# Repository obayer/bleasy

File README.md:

BLEasy
======

Arduino/HM10 based sensor plattform

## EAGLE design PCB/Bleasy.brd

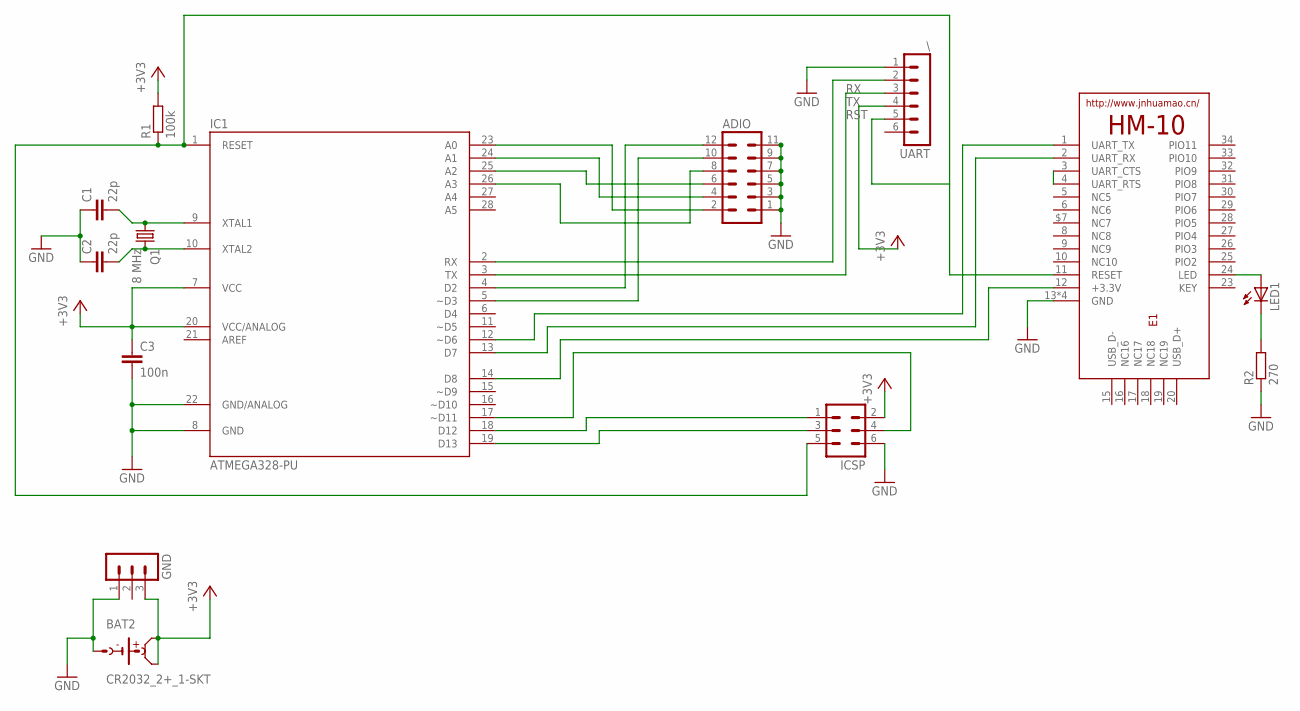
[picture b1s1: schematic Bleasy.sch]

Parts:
ADIO: MA06-2
BAT2: CR2032_2+_1-SKT; CR2032-SOCKET-THT
C1, C2: 22p; C025-025X050
C3: 100n; C025-025X050
E1: HM-10-BOARD; 26.9X13X2.2_BOARD
GND: MA03-1
IC1: ATMEGA328-PU; DIL28-3
ICSP: MA03-2
LED1: LED3MM
Q1: 8 MHz; HC49U70
R1: 100k; R1206
R2: 270; R1206
UART: \; MA06-1

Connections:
+3V3: BAT2.2 (POS2), BAT2.3 (POS1), C3.1, GND.3, IC1.7 (VCC), IC1.20 (VCC/ANALOG), ICSP.2, R1.2, UART.4
GND: ADIO.1, ADIO.3, ADIO.5, ADIO.7, ADIO.9, ADIO.11, BAT2.1 (NEG), C1.1, C2.1, C3.2, E1.13 (GND), E1.14 (GND), E1.21 (GND), E1.22 (GND), GND.1, IC1.8 (GND), IC1.22 (GND/ANALOG), ICSP.6, R2.1, UART.1
HM10_RX: E1.2 (UART_RX), IC1.13 (D7)
HM10_TX: E1.1 (UART_TX), IC1.12 (~D6)
MISO: IC1.18 (D12), ICSP.1
unnamed: C2.2, IC1.10 (XTAL2), Q1.2
unnamed: C1.2, IC1.9 (XTAL1), Q1.1
unnamed: IC1.17 (~D11), ICSP.4
unnamed: ADIO.12, IC1.4 (D2)
unnamed: ADIO.10, IC1.5 (~D3)
unnamed: E1.24 (LED), LED1.A
unnamed: LED1.K (C), R2.2
unnamed: E1.12 (+3.3V), IC1.14 (D8)
unnamed: ADIO.2, IC1.23 (A0)
unnamed: ADIO.4, IC1.24 (A1)
unnamed: ADIO.6, IC1.25 (A2)
unnamed: ADIO.8, IC1.26 (A3)
unnamed: E1.3 (UART_CTS), E1.4 (UART_RTS)
RST: E1.11 (RESET), IC1.1 (RESET), ICSP.5, R1.1, UART.5
RX: IC1.2 (RX), UART.2
SCK: IC1.19 (D13), ICSP.3
TX: IC1.3 (TX), UART.3

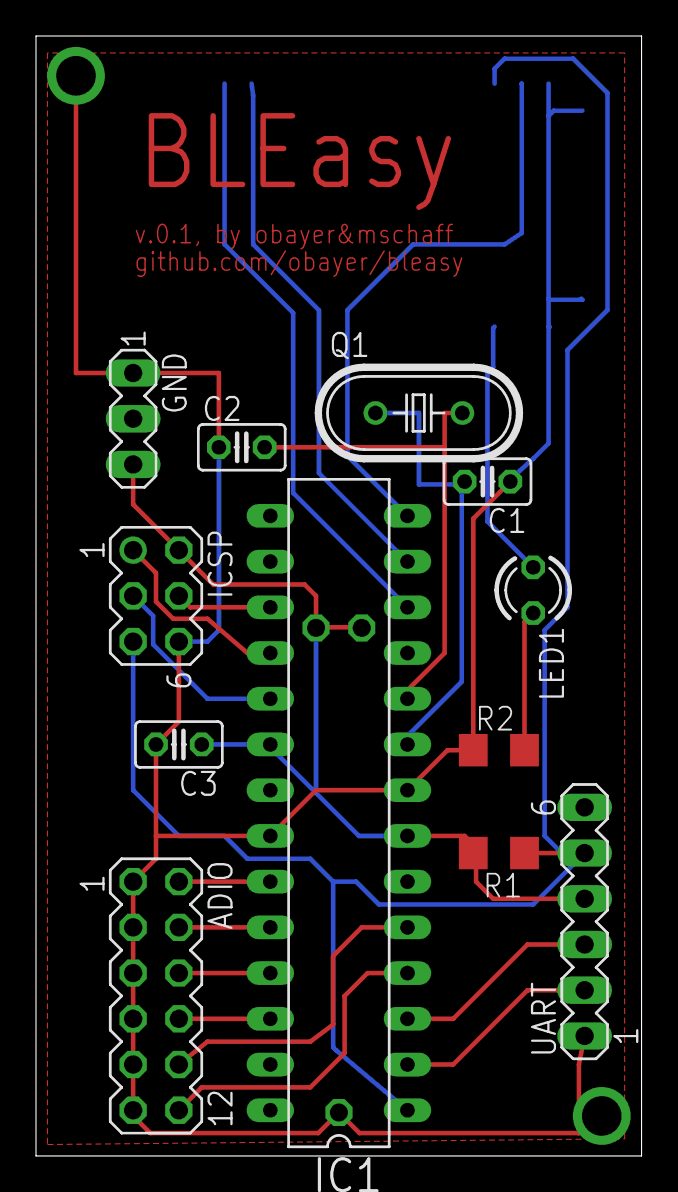
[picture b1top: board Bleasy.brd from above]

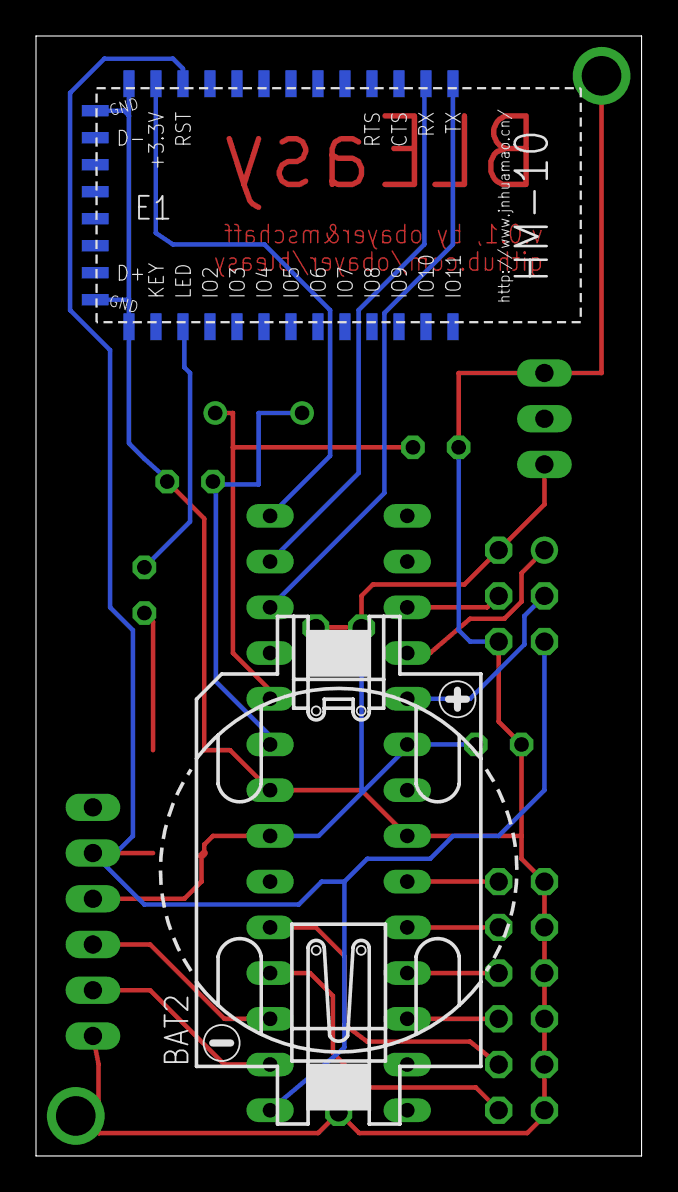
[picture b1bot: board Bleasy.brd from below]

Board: 2 copper layers, 33.6 x 62.2 mm, 14 parts (2 on the bottom side), 22 nets.

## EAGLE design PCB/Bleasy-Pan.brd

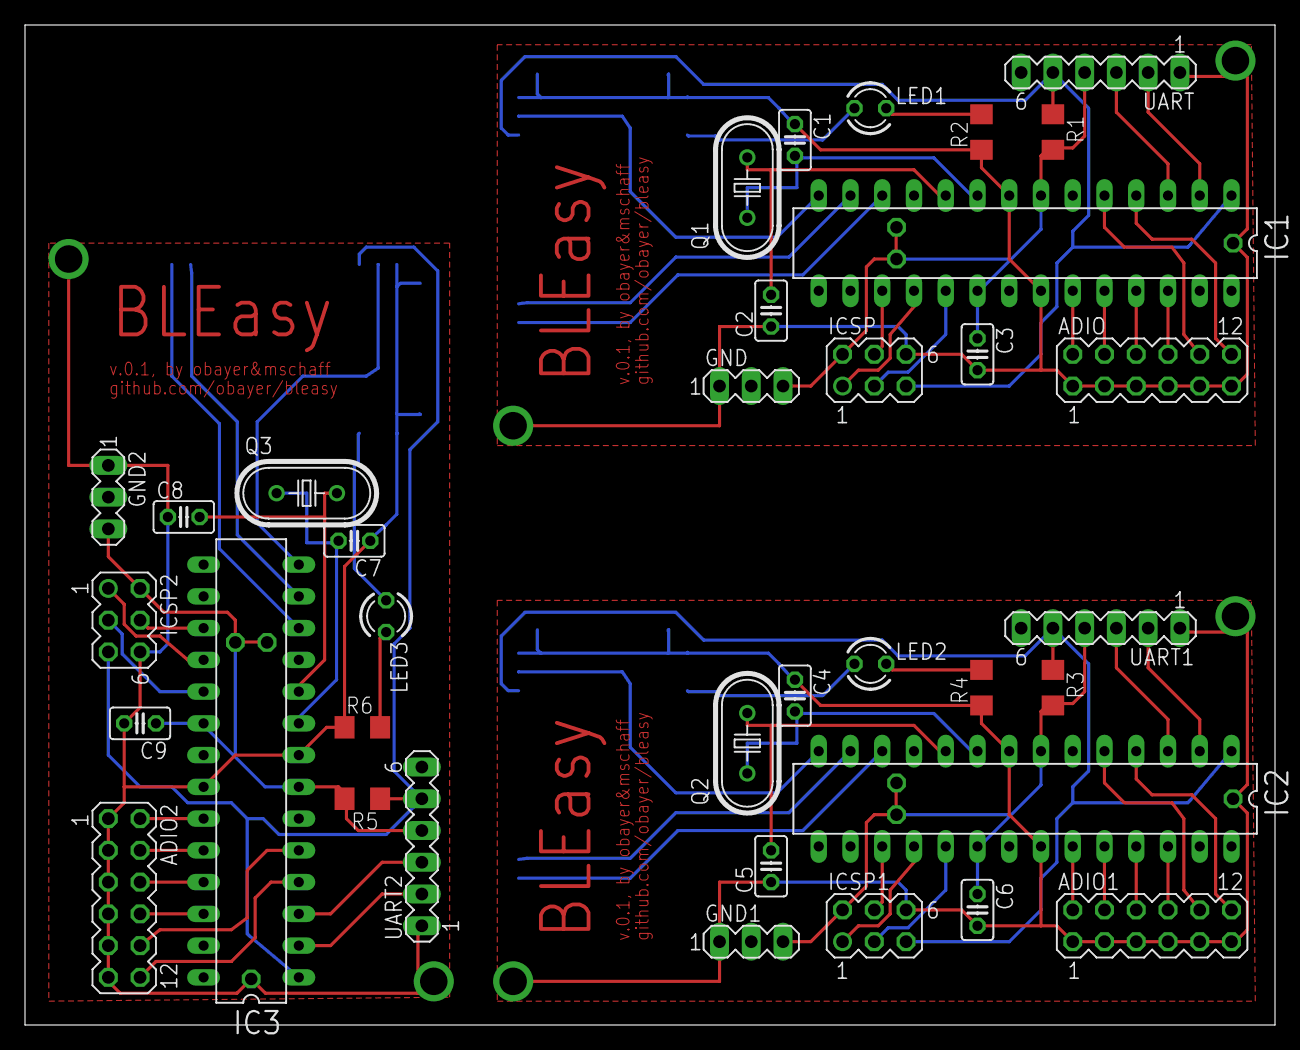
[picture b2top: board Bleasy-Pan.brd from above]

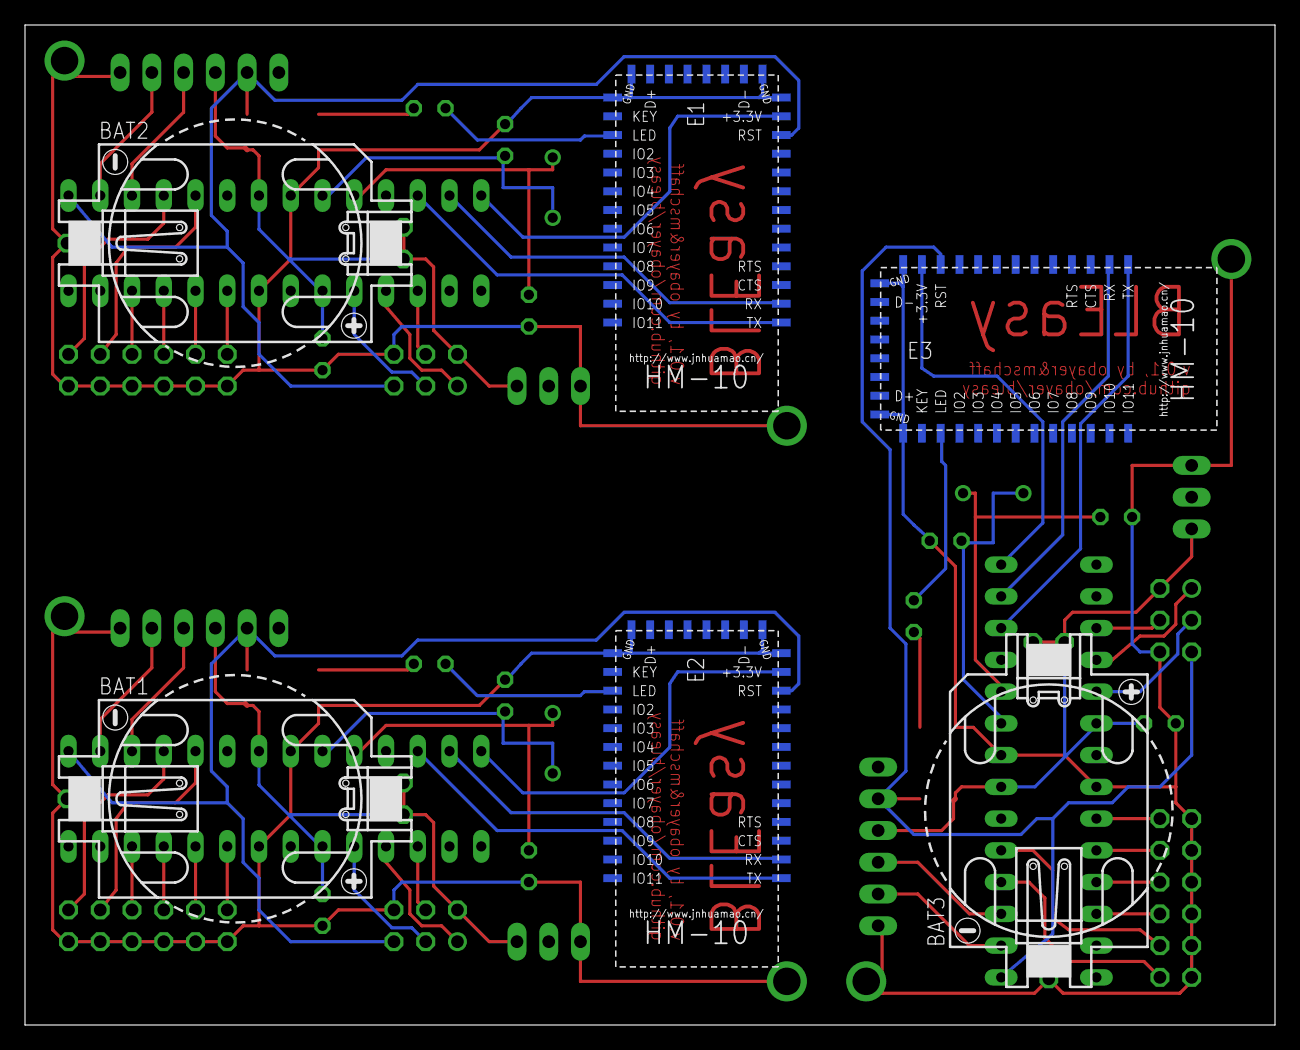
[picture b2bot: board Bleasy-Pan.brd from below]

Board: 2 copper layers, 100.0 x 80.0 mm, 42 parts (6 on the bottom side), 66 nets.

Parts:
ADIO, ADIO1, ADIO2: MA06-2
BAT1, BAT2, BAT3: CR2032_2+_1-SKT; CR2032-SOCKET-THT
C1, C2, C4, C5, C7, C8: 22p; C025-025X050
C3, C6, C9: 100n; C025-025X050
E1, E2, E3: HM-10-BOARD; 26.9X13X2.2_BOARD
GND, GND1, GND2: MA03-1
IC1, IC2, IC3: ATMEGA328-PU; DIL28-3
ICSP, ICSP1, ICSP2: MA03-2
LED1, LED2, LED3: LED3MM
Q1, Q2, Q3: 8 MHz; HC49U70
R1, R3, R5: 100k; R1206
R2, R4, R6: 270; R1206
UART, UART1, UART2: \; MA06-1

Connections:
+3V1: BAT1.2, BAT1.3, C6.1, GND1.3, IC2.7, IC2.20, ICSP1.2, R3.2, UART1.4
+3V2: BAT3.2, BAT3.3, C9.1, GND2.3, IC3.7, IC3.20, ICSP2.2, R5.2, UART2.4
+3V3: BAT2.2, BAT2.3, C3.1, GND.3, IC1.7, IC1.20, ICSP.2, R1.2, UART.4
GND: ADIO.1, ADIO.3, ADIO.5, ADIO.7, ADIO.9, ADIO.11, BAT2.1, C1.1, C2.1, C3.2, E1.13, E1.14, E1.21, E1.22, GND.1, IC1.8, IC1.22, ICSP.6, R2.1, UART.1
GND1: ADIO1.1, ADIO1.3, ADIO1.5, ADIO1.7, ADIO1.9, ADIO1.11, BAT1.1, C4.1, C5.1, C6.2, E2.13, E2.14, E2.21, E2.22, GND1.1, IC2.8, IC2.22, ICSP1.6, R4.1, UART1.1
GND2: ADIO2.1, ADIO2.3, ADIO2.5, ADIO2.7, ADIO2.9, ADIO2.11, BAT3.1, C7.1, C8.1, C9.2, E3.13, E3.14, E3.21, E3.22, GND2.1, IC3.8, IC3.22, ICSP2.6, R6.1, UART2.1
HM10_RX: E1.2, IC1.13
HM10_RX1: E2.2, IC2.13
HM10_RX2: E3.2, IC3.13
HM10_TX: E1.1, IC1.12
HM10_TX1: E2.1, IC2.12
HM10_TX2: E3.1, IC3.12
MISO: IC1.18, ICSP.1
MISO1: IC2.18, ICSP1.1
MISO2: IC3.18, ICSP2.1
unnamed: C2.2, IC1.10, Q1.2
unnamed: C1.2, IC1.9, Q1.1
unnamed: IC1.17, ICSP.4
unnamed: ADIO.12, IC1.4
unnamed: ADIO.10, IC1.5
unnamed: E1.24, LED1.A
unnamed: LED1.K, R2.2
unnamed: E1.12, IC1.14
unnamed: ADIO.2, IC1.23
unnamed: ADIO.4, IC1.24
unnamed: ADIO.6, IC1.25
unnamed: ADIO.8, IC1.26
unnamed: E1.3, E1.4
unnamed: C5.2, IC2.10, Q2.2
unnamed: C4.2, IC2.9, Q2.1
unnamed: IC2.17, ICSP1.4
unnamed: E2.12, IC2.14
unnamed: E2.24, LED2.A
unnamed: LED2.K, R4.2
unnamed: E2.3, E2.4
unnamed: ADIO1.12, IC2.4
unnamed: ADIO1.10, IC2.5
unnamed: ADIO1.2, IC2.23
unnamed: ADIO1.4, IC2.24
unnamed: ADIO1.6, IC2.25
unnamed: ADIO1.8, IC2.26
unnamed: C8.2, IC3.10, Q3.2
unnamed: C7.2, IC3.9, Q3.1
unnamed: IC3.17, ICSP2.4
unnamed: E3.12, IC3.14
unnamed: E3.24, LED3.A
unnamed: LED3.K, R6.2
unnamed: E3.3, E3.4
unnamed: ADIO2.12, IC3.4
unnamed: ADIO2.10, IC3.5
unnamed: ADIO2.2, IC3.23
unnamed: ADIO2.4, IC3.24
unnamed: ADIO2.6, IC3.25
unnamed: ADIO2.8, IC3.26
RST: E1.11, IC1.1, ICSP.5, R1.1, UART.5
RST1: E2.11, IC2.1, ICSP1.5, R3.1, UART1.5
RST2: E3.11, IC3.1, ICSP2.5, R5.1, UART2.5
RX: IC1.2, UART.2
RX1: IC2.2, UART1.2
RX2: IC3.2, UART2.2
SCK: IC1.19, ICSP.3
SCK1: IC2.19, ICSP1.3
SCK2: IC3.19, ICSP2.3
TX: IC1.3, UART.3
TX1: IC2.3, UART1.3
TX2: IC3.3, UART2.3

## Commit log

2014-07-23 initial cheHM-10 serial comm
2014-07-31 merged power savings and state machine
2014-07-31 chore(git): Add eagle project file to git ignore
2014-07-31 feat(pcb): Added first PCB layout
2014-08-04 New cell coin adapter
2014-08-04 new board layout
2014-08-04 board: removed via under hm10
2014-08-09 minor board changes, added Text
2014-08-10 fix: Added missing GND line
2014-08-10 add: SketchUp 3d model
2014-08-11 reordered Pingheaders, SMD
2014-08-11 added ground plane
2014-08-11 ground plane with gap
2014-08-11 refactor(PCB): Increased isolation width between signal traces and ground plane
2014-08-11 refactor(PCB): Moved UART pinheader some millimeters away from the drilling hole
2014-08-11 feat(3dmodel): Created new 3d model of the pcb
2014-08-18 Renamed project
2014-08-18 Renamed pcb lettering
2014-08-20 feat(Panelize): Added panelized board.
2014-08-29 adaptet pin setup for dvt sample
2014-08-29 set correct RX/TX in avr softserial
2014-08-29 correct power pin
2014-09-01 added auto wake after 8sec
2014-09-04 doc(README): Changed project name
